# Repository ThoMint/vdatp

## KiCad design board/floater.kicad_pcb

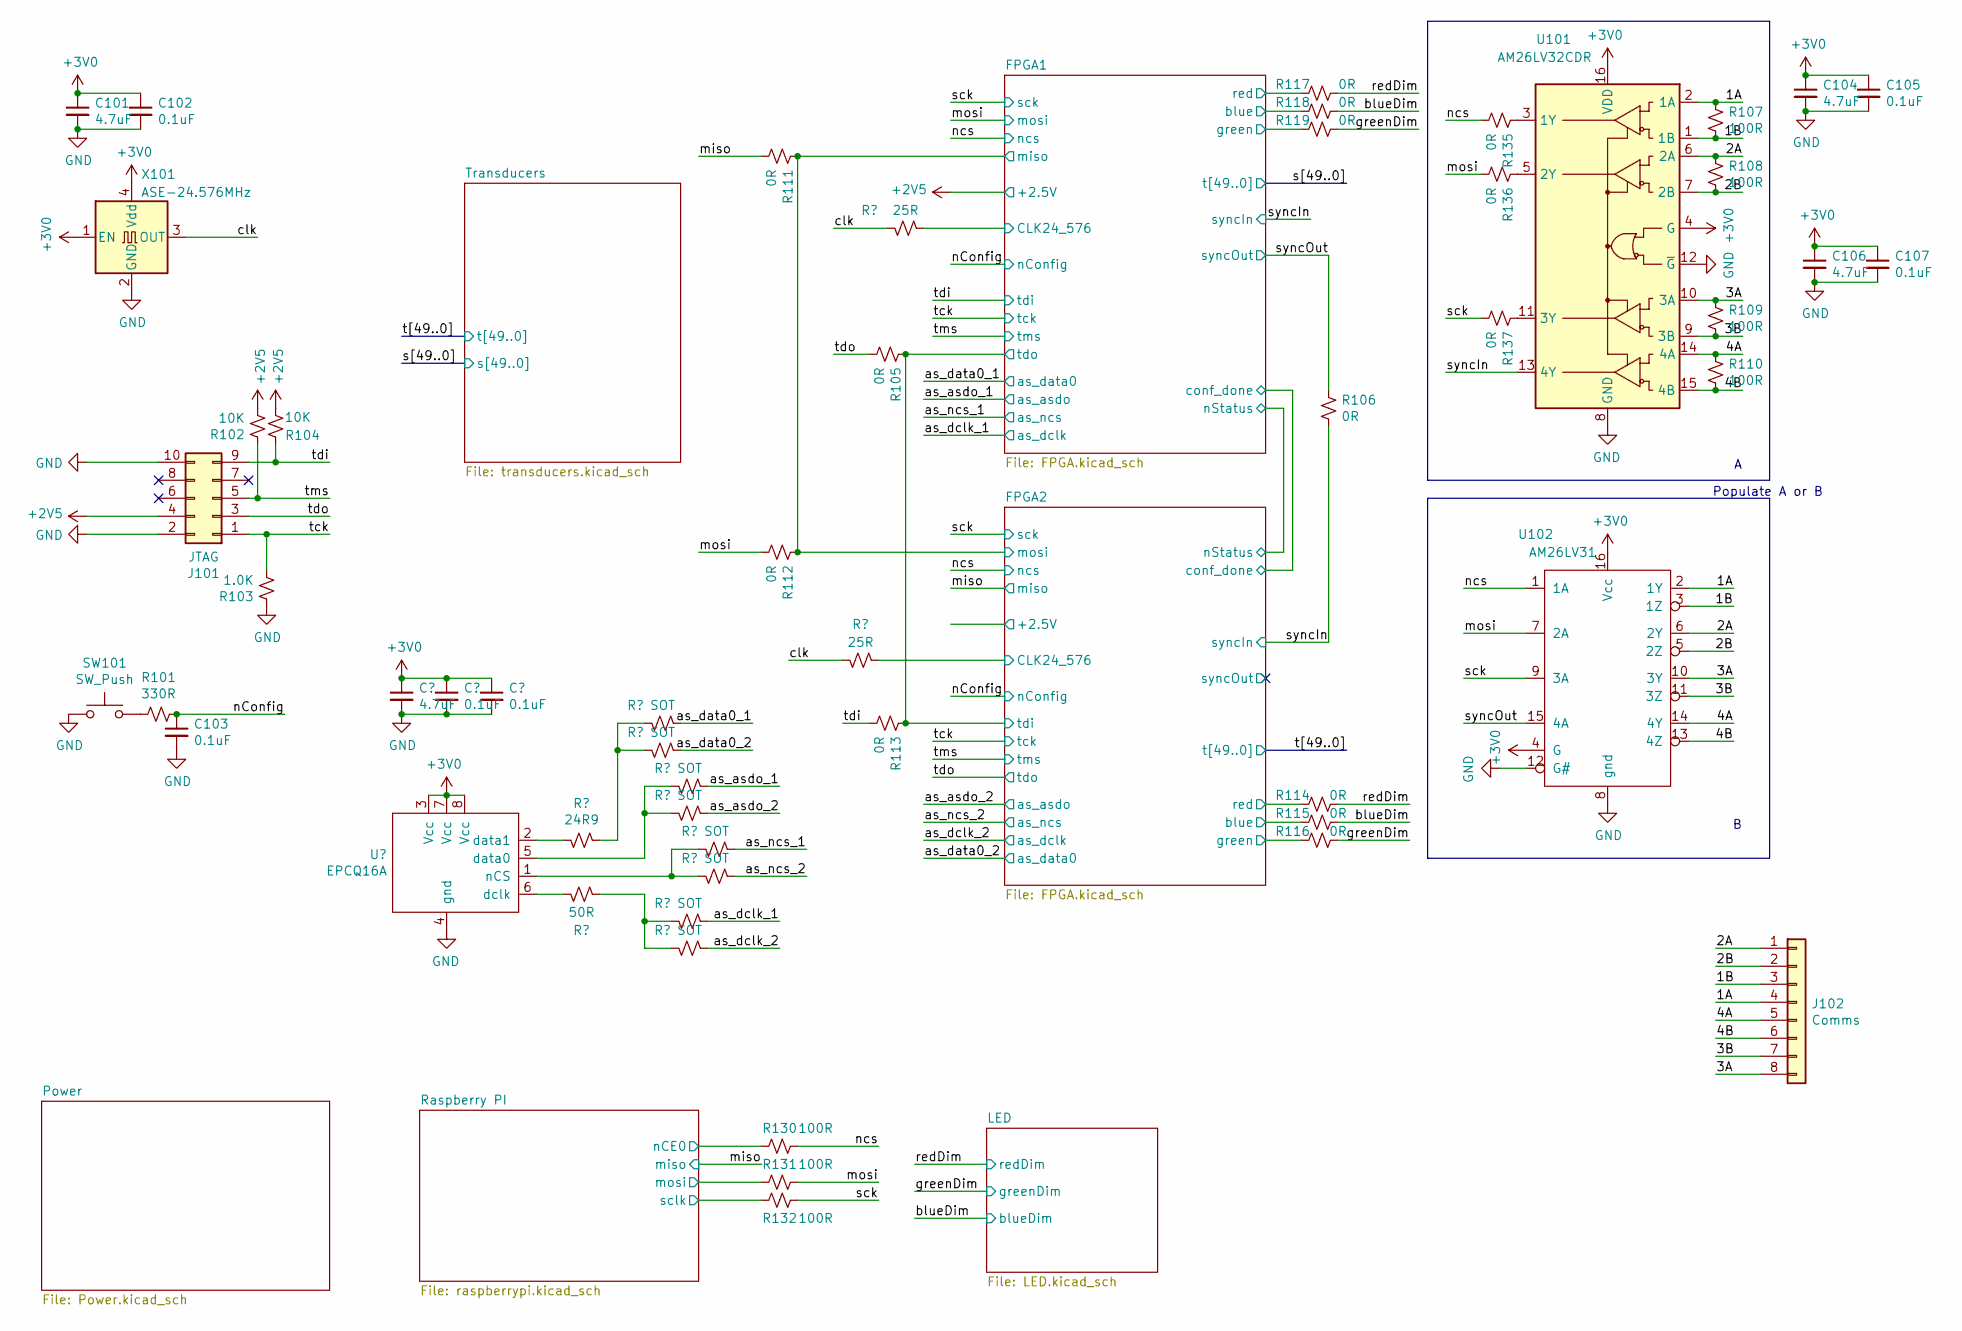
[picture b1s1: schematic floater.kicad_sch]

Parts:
C101, C104, C106, C108: 4.7uF; C_0603_1608Metric
C102, C103, C105, C107, C109, C110: 0.1uF; C_0402_1005Metric
J101: JTAG; PinHeader_2x05_P2.54mm_Vertical_Shrouded
J102: Comms; Hirose_DF13-08P-1.25DS_1x08_P1.25mm_Horizontal
R101: 330R; R_0402_1005Metric
R102, R104: 10K; R_0402_1005Metric
R103: 1.0K; R_0402_1005Metric
R105, R111, R112, R113, R114, R115, R116, R117, R118, R119, R135, R136, R137: 0R; R_0402_1005Metric
R106: 0R; SolderJumper-2_P1.3mm_Open_TrianglePad1.0x1.5mm
R107, R108, R109, R110, R130, R131, R132: 100R; R_0402_1005Metric
R120: 24R9; R_0402_1005Metric
R121: 50R; R_0402_1005Metric
R122, R123, R124, R125, R126, R127, R128, R129: SOT; R_0402_1005Metric
R133, R134: 25R; R_0402_1005Metric
SW101: SW_Push; SW_SPST_KMR2
U101: AM26LV32CDR; SOIC-16_3.9x9.9mm_P1.27mm
U102: AM26LV31; SOIC-16_3.9x9.9mm_P1.27mm
U103: EPCQ16A; SOIC-8_3.9x4.9mm_P1.27mm
X101: ASE-24.576MHz; ASFL1

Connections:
+3V0: C101.1, C102.1, C104.1, C105.1, C106.1, C107.1, C108.1, C109.1, C110.1, U101.4 (G), U101.16 (VDD), U102.4 (G), U102.16 (Vcc), U103.3 (Vcc), U103.7 (Vcc), U103.8 (Vcc), X101.1 (EN), X101.4 (Vdd); also elsewhere on the board
/1A: J102.4, R107.1, U101.2 (1A), U102.2 (1Y)
/1B: J102.3, R107.2, U101.1 (1B), U102.3 (1Z)
/2A: J102.1, R108.1, U101.6 (2A), U102.6 (2Y)
/2B: J102.2, R108.2, U101.7 (2B), U102.5 (2Z)
/3A: J102.8, R109.1, U101.10 (3A), U102.10 (3Y)
/3B: J102.7, R109.2, U101.9 (3B), U102.11 (3Z)
/4A: J102.5, R110.1, U101.14 (4A), U102.14 (4Y)
/4B: J102.6, R110.2, U101.15 (4B), U102.13 (4Z)
/FPGA1/CLK24_576: R134.2; also elsewhere on the board
/FPGA1/blue: R118.2; also elsewhere on the board
/FPGA1/green: R119.2; also elsewhere on the board
/FPGA1/miso: R111.1, R112.1; also elsewhere on the board
/FPGA1/red: R117.2; also elsewhere on the board
/FPGA2/CLK24_576: R133.2; also elsewhere on the board
/FPGA2/blue: R115.2; also elsewhere on the board
/FPGA2/green: R116.2; also elsewhere on the board
/FPGA2/red: R114.2; also elsewhere on the board
/FPGA2/tdi: R105.1, R113.1; also elsewhere on the board
/Raspberry PI/mosi: R131.2; also elsewhere on the board
/Raspberry PI/nCE0: R130.2; also elsewhere on the board
/Raspberry PI/sclk: R132.2; also elsewhere on the board
/as_asdo_1: R124.2; also elsewhere on the board
/as_asdo_2: R125.2; also elsewhere on the board
/as_data0_1: R122.2; also elsewhere on the board
/as_data0_2: R123.2; also elsewhere on the board
/as_dclk_1: R126.2; also elsewhere on the board
/as_dclk_2: R127.2; also elsewhere on the board
/as_ncs_1: R128.2; also elsewhere on the board
/as_ncs_2: R129.2; also elsewhere on the board
/blueDim: R115.1, R118.1; also elsewhere on the board
/clk: R133.1, R134.1, X101.3 (OUT)
/greenDim: R116.1, R119.1; also elsewhere on the board
/miso: R111.2; also elsewhere on the board
/mosi: R112.2, R131.1, R136.2, U102.7 (2A); also elsewhere on the board
/nConfig: C103.1, R101.2; also elsewhere on the board
/ncs: R130.1, R135.2, U102.1 (1A); also elsewhere on the board
/redDim: R114.1, R117.1; also elsewhere on the board
/sck: R132.1, R137.2, U102.9 (3A); also elsewhere on the board
/syncIn: R106.2, U101.13 (4Y); also elsewhere on the board
/syncOut: R106.1, U102.15 (4A); also elsewhere on the board
/tck: J101.1, R103.2; also elsewhere on the board
/tdi: J101.9, R104.1, R113.2; also elsewhere on the board
/tdo: J101.3, R105.2; also elsewhere on the board
/tms: J101.5, R102.1; also elsewhere on the board
GND: C101.2, C102.2, C103.2, C104.2, C105.2, C106.2, C107.2, C108.2, C109.2, C110.2, J101.2, J101.10, R103.1, SW101.1, U101.8 (GND), U101.12 (~G), U102.8 (gnd), U102.12 (G#), U103.4 (gnd), X101.2 (GND); also elsewhere on the board
unnamed: R101.1, SW101.2
unnamed: R120.1, U103.2 (data1)
unnamed: R120.2, R122.1, R123.1
unnamed: R121.1, U103.6 (dclk)
unnamed: R121.2, R126.1, R127.1
unnamed: R124.1, R125.1, U103.5 (data0)
unnamed: R128.1, R129.1, U103.1 (nCS)
unnamed: R135.1, U101.3 (1Y)
unnamed: R136.1, U101.5 (2Y)
unnamed: R137.1, U101.11 (3Y)

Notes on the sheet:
Populate A or B

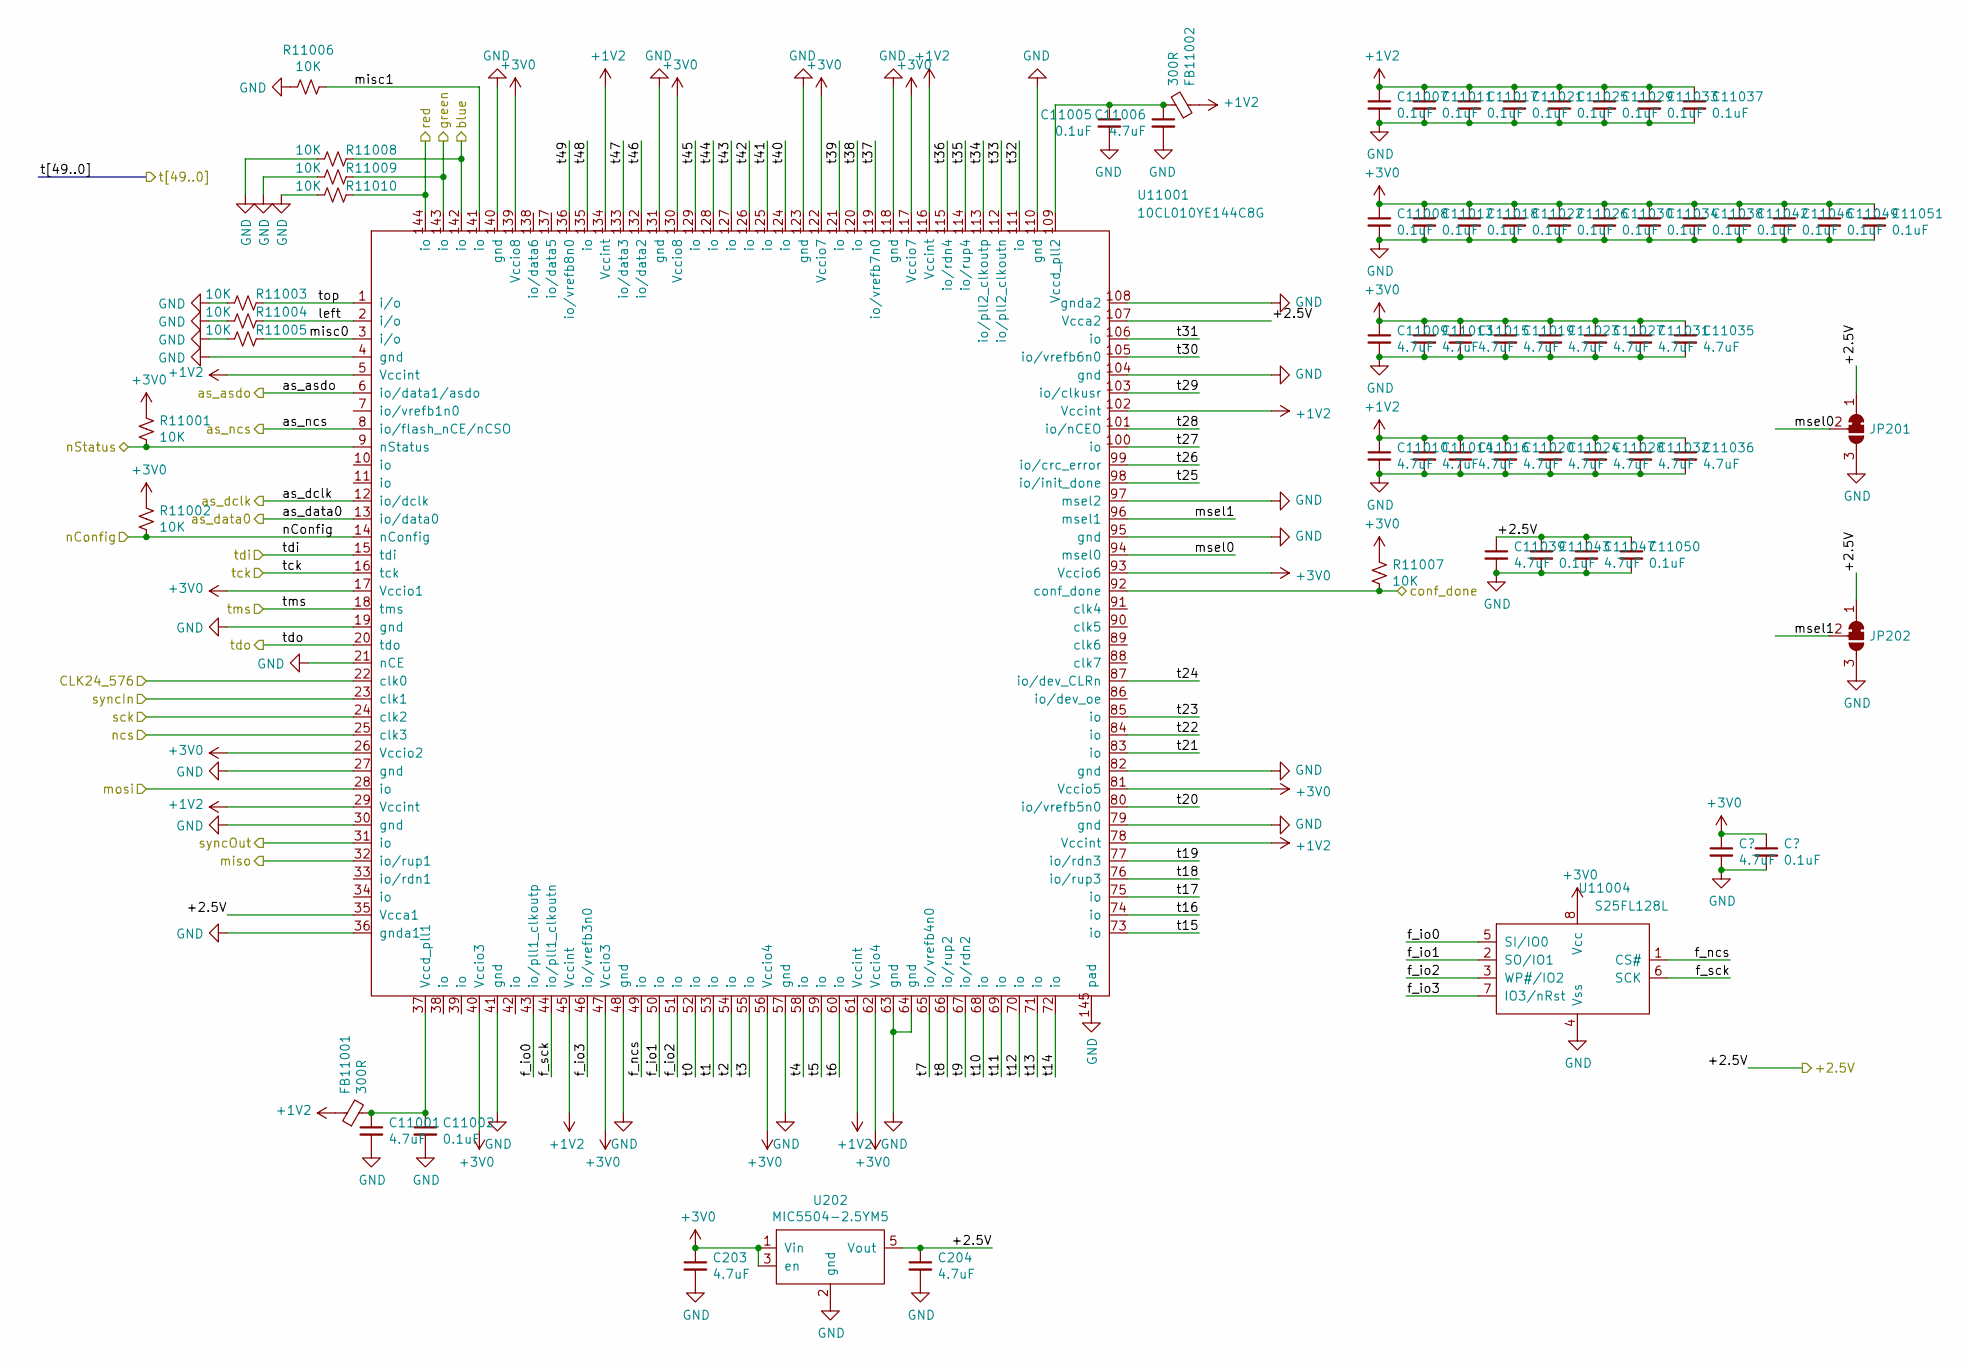
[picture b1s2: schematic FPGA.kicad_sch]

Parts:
C203, C204, C241, C11001, C11006, C11009, C11010, C11013, C11014, C11015, C11016, C11019, C11020, C11023, C11024, C11027, C11028, C11031, C11032, C11035, C11036, C11039, C11047: 4.7uF; C_0603_1608Metric
C245, C11002, C11005, C11007, C11008, C11011, C11012, C11017, C11018, C11021, C11022, C11025, C11026, C11029, C11030, C11033, C11034, C11037, C11038, C11042, C11043, C11046, C11049, C11050, C11051: 0.1uF; C_0402_1005Metric
FB11001, FB11002: 300R; R_0402_1005Metric
JP201, JP202: SolderJumper_3_Bridged12; SolderJumper-3_bridged12
R11001, R11002, R11003, R11004, R11005, R11006, R11007, R11008, R11009, R11010: 10K; R_0402_1005Metric
U202: MIC5504-2.5YM5; SOT-23-5
U11001: 10CL010YE144C8G; EQFP-144-1EP_20x20mm_P0.5mm_EP6.7x6.7mm
U11004: S25FL128L; SOIC-8_5.275x5.275mm_P1.27mm

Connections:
+1V2: C11007.1, C11010.1, C11011.1, C11014.1, C11016.1, C11017.1, C11020.1, C11021.1, C11024.1, C11025.1, C11028.1, C11029.1, C11032.1, C11033.1, C11036.1, C11037.1, FB11001.1, FB11002.1, U11001.5 (Vccint), U11001.29 (Vccint), U11001.45 (Vccint), U11001.61 (Vccint), U11001.78 (Vccint), U11001.102 (Vccint), U11001.116 (Vccint), U11001.134 (Vccint); also elsewhere on the board
+3V0: C203.1, C241.1, C245.1, C11008.1, C11009.1, C11012.1, C11013.1, C11015.1, C11018.1, C11019.1, C11022.1, C11023.1, C11026.1, C11027.1, C11030.1, C11031.1, C11034.1, C11035.1, C11038.1, C11042.1, C11046.1, C11049.1, C11051.1, R11001.2, R11002.2, R11007.2, U202.1 (Vin), U202.3 (en), U11001.17 (Vccio1), U11001.26 (Vccio2), U11001.40 (Vccio3), U11001.47 (Vccio3), U11001.56 (Vccio4), U11001.62 (Vccio4), U11001.81 (Vccio5), U11001.93 (Vccio6), U11001.117 (Vccio7), U11001.122 (Vccio7), U11001.130 (Vccio8), U11001.139 (Vccio8), U11004.8 (Vcc); also elsewhere on the board
/FPGA1/conf_done: R11007.1, U11001.92 (conf_done); also elsewhere on the board
/FPGA1/miso: U11001.28 (io); also elsewhere on the board
/FPGA1/nStatus: R11001.1, U11001.9 (nStatus); also elsewhere on the board
/FPGA2/CLK24_576: U11001.22 (clk0); also elsewhere on the board
/FPGA2/blue: R11008.2, U11001.142 (io); also elsewhere on the board
/FPGA2/f_io0: U11001.43 (io/pll1_clkoutp), U11004.5 (SI/IO0)
/FPGA2/f_io1: U11001.50 (io), U11004.2 (SO/IO1)
/FPGA2/f_io2: U11001.51 (io), U11004.3 (WP#/IO2)
/FPGA2/f_io3: U11001.46 (io/vrefb3n0), U11004.7 (IO3/nRst)
/FPGA2/f_ncs: U11001.49 (io), U11004.1 (CS#)
/FPGA2/f_sck: U11001.44 (io/pll1_clkoutn), U11004.6 (SCK)
/FPGA2/green: R11009.2, U11001.143 (io); also elsewhere on the board
/FPGA2/left: R11004.2, U11001.2 (i/o)
/FPGA2/misc0: R11005.2, U11001.3 (i/o)
/FPGA2/misc1: R11006.2, U11001.141 (io)
/FPGA2/red: R11010.2, U11001.144 (io); also elsewhere on the board
/FPGA2/syncOut: U11001.31 (io)
/FPGA2/t0: U11001.52 (io); also elsewhere on the board
/FPGA2/t1: U11001.53 (io); also elsewhere on the board
/FPGA2/t2: U11001.54 (io); also elsewhere on the board
/FPGA2/t3: U11001.55 (io); also elsewhere on the board
/FPGA2/t4: U11001.58 (io); also elsewhere on the board
/FPGA2/t5: U11001.59 (io); also elsewhere on the board
/FPGA2/t6: U11001.60 (io); also elsewhere on the board
/FPGA2/t7: U11001.65 (io/vrefb4n0); also elsewhere on the board
/FPGA2/t8: U11001.66 (io/rup2); also elsewhere on the board
/FPGA2/t9: U11001.67 (io/rdn2); also elsewhere on the board
/FPGA2/t10: U11001.68 (io); also elsewhere on the board
/FPGA2/t11: U11001.69 (io); also elsewhere on the board
/FPGA2/t12: U11001.70 (io); also elsewhere on the board
/FPGA2/t13: U11001.71 (io); also elsewhere on the board
/FPGA2/t14: U11001.72 (io); also elsewhere on the board
/FPGA2/t15: U11001.73 (io); also elsewhere on the board
/FPGA2/t16: U11001.74 (io); also elsewhere on the board
/FPGA2/t17: U11001.75 (io); also elsewhere on the board
/FPGA2/t18: U11001.76 (io/rup3); also elsewhere on the board
/FPGA2/t19: U11001.77 (io/rdn3); also elsewhere on the board
/FPGA2/t20: U11001.80 (io/vrefb5n0); also elsewhere on the board
/FPGA2/t21: U11001.83 (io); also elsewhere on the board
/FPGA2/t22: U11001.84 (io); also elsewhere on the board
/FPGA2/t23: U11001.85 (io); also elsewhere on the board
/FPGA2/t24: U11001.87 (io/dev_CLRn); also elsewhere on the board
/FPGA2/t25: U11001.98 (io/init_done); also elsewhere on the board
/FPGA2/t26: U11001.99 (io/crc_error); also elsewhere on the board
/FPGA2/t27: U11001.100 (io); also elsewhere on the board
/FPGA2/t28: U11001.101 (io/nCEO); also elsewhere on the board
/FPGA2/t29: U11001.103 (io/clkusr); also elsewhere on the board
/FPGA2/t30: U11001.105 (io/vrefb6n0); also elsewhere on the board
/FPGA2/t31: U11001.106 (io); also elsewhere on the board
/FPGA2/t32: U11001.111 (io); also elsewhere on the board
/FPGA2/t33: U11001.112 (io/pll2_clkoutn); also elsewhere on the board
/FPGA2/t34: U11001.113 (io/pll2_clkoutp); also elsewhere on the board
/FPGA2/t35: U11001.114 (io/rup4); also elsewhere on the board
/FPGA2/t36: U11001.115 (io/rdn4); also elsewhere on the board
/FPGA2/t37: U11001.119 (io/vrefb7n0); also elsewhere on the board
/FPGA2/t38: U11001.120 (io); also elsewhere on the board
/FPGA2/t39: U11001.121 (io); also elsewhere on the board
/FPGA2/t40: U11001.124 (io); also elsewhere on the board
/FPGA2/t41: U11001.125 (io); also elsewhere on the board
/FPGA2/t42: U11001.126 (io); also elsewhere on the board
/FPGA2/t43: U11001.127 (io); also elsewhere on the board
/FPGA2/t44: U11001.128 (io); also elsewhere on the board
/FPGA2/t45: U11001.129 (io); also elsewhere on the board
/FPGA2/t46: U11001.132 (io/data2); also elsewhere on the board
/FPGA2/t47: U11001.133 (io/data3); also elsewhere on the board
/FPGA2/t48: U11001.135 (io); also elsewhere on the board
/FPGA2/t49: U11001.136 (io/vrefb8n0); also elsewhere on the board
/FPGA2/tdi: U11001.15 (tdi); also elsewhere on the board
/FPGA2/top: R11003.2, U11001.1 (i/o)
/as_asdo_2: U11001.6 (io/data1/asdo); also elsewhere on the board
/as_data0_2: U11001.13 (io/data0); also elsewhere on the board
/as_dclk_2: U11001.12 (io/dclk); also elsewhere on the board
/as_ncs_2: U11001.8 (io/flash_nCE/nCSO); also elsewhere on the board
/miso: U11001.32 (io/rup1); also elsewhere on the board
/nConfig: R11002.1, U11001.14 (nConfig); also elsewhere on the board
/ncs: U11001.25 (clk3); also elsewhere on the board
/sck: U11001.24 (clk2); also elsewhere on the board
/syncIn: U11001.23 (clk1); also elsewhere on the board
/tck: U11001.16 (tck); also elsewhere on the board
/tdo: U11001.20 (tdo); also elsewhere on the board
/tms: U11001.18 (tms); also elsewhere on the board
GND: C203.2, C204.2, C241.2, C245.2, C11001.2, C11002.2, C11005.2, C11006.2, C11007.2, C11008.2, C11009.2, C11010.2, C11011.2, C11012.2, C11013.2, C11014.2, C11015.2, C11016.2, C11017.2, C11018.2, C11019.2, C11020.2, C11021.2, C11022.2, C11023.2, C11024.2, C11025.2, C11026.2, C11027.2, C11028.2, C11029.2, C11030.2, C11031.2, C11032.2, C11033.2, C11034.2, C11035.2, C11036.2, C11037.2, C11038.2, C11039.2, C11042.2, C11043.2, C11046.2, C11047.2, C11049.2, C11050.2, C11051.2, JP201.3 (B), JP202.3 (B), R11003.1, R11004.1, R11005.1, R11006.1, R11008.1, R11009.1, R11010.1, U202.2 (gnd), U11001.4 (gnd), U11001.19 (gnd), U11001.21 (nCE), U11001.27 (gnd), U11001.30 (gnd), U11001.36 (gnda1), U11001.41 (gnd), U11001.48 (gnd), U11001.57 (gnd), U11001.63 (gnd), U11001.64 (gnd), U11001.79 (gnd), U11001.82 (gnd), U11001.95 (gnd), U11001.97 (msel2), U11001.104 (gnd), U11001.108 (gnda2), U11001.110 (gnd), U11001.118 (gnd), U11001.123 (gnd), U11001.131 (gnd), U11001.140 (gnd), U11001.145 (pad), U11004.4 (Vss); also elsewhere on the board
unnamed: C11001.1, C11002.1, FB11001.2, U11001.37 (Vccd_pll1)
unnamed: C11005.1, C11006.1, FB11002.2, U11001.109 (Vccd_pll2)

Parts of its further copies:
C201, C206, C209, C210, C213, C214, C215, C216, C219, C220, C223, C224, C227, C228, C231, C232, C235, C236, C239, C247, C11003, C11004, C11041: 4.7uF; C_0603_1608Metric
C202, C205, C207, C208, C211, C212, C217, C218, C221, C222, C225, C226, C229, C230, C233, C234, C237, C238, C242, C243, C246, C249, C250, C251, C11045: 0.1uF; C_0402_1005Metric
FB201, FB202: 300R; R_0402_1005Metric
JP11001, JP11002: SolderJumper_3_Bridged12; SolderJumper-3_bridged12
R201, R202, R203, R204, R205, R206, R207, R208, R209, R210: 10K; R_0402_1005Metric
U201: 10CL010YE144C8G; EQFP-144-1EP_20x20mm_P0.5mm_EP6.7x6.7mm
U204: S25FL128L; SOIC-8_5.275x5.275mm_P1.27mm
U11002: MIC5504-2.5YM5; SOT-23-5

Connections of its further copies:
+1V2: C207.1, C210.1, C211.1, C214.1, C216.1, C217.1, C220.1, C221.1, C224.1, C225.1, C228.1, C229.1, C232.1, C233.1, C236.1, C237.1, FB201.1, FB202.1, U201.5 (Vccint), U201.29 (Vccint), U201.45 (Vccint), U201.61 (Vccint), U201.78 (Vccint), U201.102 (Vccint), U201.116 (Vccint), U201.134 (Vccint); also elsewhere on the board
+3V0: C208.1, C209.1, C212.1, C213.1, C215.1, C218.1, C219.1, C222.1, C223.1, C226.1, C227.1, C230.1, C231.1, C234.1, C235.1, C238.1, C242.1, C246.1, C249.1, C251.1, C11003.1, C11041.1, C11045.1, R201.2, R202.2, R207.2, U201.17 (Vccio1), U201.26 (Vccio2), U201.40 (Vccio3), U201.47 (Vccio3), U201.56 (Vccio4), U201.62 (Vccio4), U201.81 (Vccio5), U201.93 (Vccio6), U201.117 (Vccio7), U201.122 (Vccio7), U201.130 (Vccio8), U201.139 (Vccio8), U204.8 (Vcc), U11002.1 (Vin), U11002.3 (en); also elsewhere on the board
/FPGA1/CLK24_576: U201.22 (clk0); also elsewhere on the board
/FPGA1/blue: R208.2, U201.142 (io); also elsewhere on the board
/FPGA1/conf_done: R207.1, U201.92 (conf_done); also elsewhere on the board
/FPGA1/f_io0: U201.43 (io/pll1_clkoutp), U204.5 (SI/IO0)
/FPGA1/f_io1: U201.50 (io), U204.2 (SO/IO1)
/FPGA1/f_io2: U201.51 (io), U204.3 (WP#/IO2)
/FPGA1/f_io3: U201.46 (io/vrefb3n0), U204.7 (IO3/nRst)
/FPGA1/f_ncs: U201.49 (io), U204.1 (CS#)
/FPGA1/f_sck: U201.44 (io/pll1_clkoutn), U204.6 (SCK)
/FPGA1/green: R209.2, U201.143 (io); also elsewhere on the board
/FPGA1/left: R204.2, U201.2 (i/o)
/FPGA1/misc0: R205.2, U201.3 (i/o)
/FPGA1/misc1: R206.2, U201.141 (io)
/FPGA1/miso: U201.32 (io/rup1); also elsewhere on the board
/FPGA1/nStatus: R201.1, U201.9 (nStatus); also elsewhere on the board
/FPGA1/red: R210.2, U201.144 (io); also elsewhere on the board
/FPGA1/top: R203.2, U201.1 (i/o)
/FPGA2/tdi: U201.20 (tdo); also elsewhere on the board
/Transducers/s0: U201.52 (io); also elsewhere on the board
/Transducers/s1: U201.53 (io); also elsewhere on the board
/Transducers/s2: U201.54 (io); also elsewhere on the board
/Transducers/s3: U201.55 (io); also elsewhere on the board
/Transducers/s4: U201.58 (io); also elsewhere on the board
/Transducers/s5: U201.59 (io); also elsewhere on the board
/Transducers/s6: U201.60 (io); also elsewhere on the board
/Transducers/s7: U201.65 (io/vrefb4n0); also elsewhere on the board
/Transducers/s8: U201.66 (io/rup2); also elsewhere on the board
/Transducers/s9: U201.67 (io/rdn2); also elsewhere on the board
/Transducers/s10: U201.68 (io); also elsewhere on the board
/Transducers/s11: U201.69 (io); also elsewhere on the board
/Transducers/s12: U201.70 (io); also elsewhere on the board
/Transducers/s13: U201.71 (io); also elsewhere on the board
/Transducers/s14: U201.72 (io); also elsewhere on the board
/Transducers/s15: U201.73 (io); also elsewhere on the board
/Transducers/s16: U201.74 (io); also elsewhere on the board
/Transducers/s17: U201.75 (io); also elsewhere on the board
/Transducers/s18: U201.76 (io/rup3); also elsewhere on the board
/Transducers/s19: U201.77 (io/rdn3); also elsewhere on the board
/Transducers/s20: U201.80 (io/vrefb5n0); also elsewhere on the board
/Transducers/s21: U201.83 (io); also elsewhere on the board
/Transducers/s22: U201.84 (io); also elsewhere on the board
/Transducers/s23: U201.85 (io); also elsewhere on the board
/Transducers/s24: U201.87 (io/dev_CLRn); also elsewhere on the board
/Transducers/s25: U201.98 (io/init_done); also elsewhere on the board
/Transducers/s26: U201.99 (io/crc_error); also elsewhere on the board
/Transducers/s27: U201.100 (io); also elsewhere on the board
/Transducers/s28: U201.101 (io/nCEO); also elsewhere on the board
/Transducers/s29: U201.103 (io/clkusr); also elsewhere on the board
/Transducers/s30: U201.105 (io/vrefb6n0); also elsewhere on the board
/Transducers/s31: U201.106 (io); also elsewhere on the board
/Transducers/s32: U201.111 (io); also elsewhere on the board
/Transducers/s33: U201.112 (io/pll2_clkoutn); also elsewhere on the board
/Transducers/s34: U201.113 (io/pll2_clkoutp); also elsewhere on the board
/Transducers/s35: U201.114 (io/rup4); also elsewhere on the board
/Transducers/s36: U201.115 (io/rdn4); also elsewhere on the board
/Transducers/s37: U201.119 (io/vrefb7n0); also elsewhere on the board
/Transducers/s38: U201.120 (io); also elsewhere on the board
/Transducers/s39: U201.121 (io); also elsewhere on the board
/Transducers/s40: U201.124 (io); also elsewhere on the board
/Transducers/s41: U201.125 (io); also elsewhere on the board
/Transducers/s42: U201.126 (io); also elsewhere on the board
/Transducers/s43: U201.127 (io); also elsewhere on the board
/Transducers/s44: U201.128 (io); also elsewhere on the board
/Transducers/s45: U201.129 (io); also elsewhere on the board
/Transducers/s46: U201.132 (io/data2); also elsewhere on the board
/Transducers/s47: U201.133 (io/data3); also elsewhere on the board
/Transducers/s48: U201.135 (io); also elsewhere on the board
/Transducers/s49: U201.136 (io/vrefb8n0); also elsewhere on the board
/as_asdo_1: U201.6 (io/data1/asdo); also elsewhere on the board
/as_data0_1: U201.13 (io/data0); also elsewhere on the board
/as_dclk_1: U201.12 (io/dclk); also elsewhere on the board
/as_ncs_1: U201.8 (io/flash_nCE/nCSO); also elsewhere on the board
/mosi: U201.28 (io); also elsewhere on the board
/nConfig: R202.1, U201.14 (nConfig); also elsewhere on the board
/ncs: U201.25 (clk3); also elsewhere on the board
/sck: U201.24 (clk2); also elsewhere on the board
/syncIn: U201.23 (clk1); also elsewhere on the board
/syncOut: U201.31 (io); also elsewhere on the board
/tck: U201.16 (tck); also elsewhere on the board
/tdi: U201.15 (tdi); also elsewhere on the board
/tms: U201.18 (tms); also elsewhere on the board
GND: C201.2, C202.2, C205.2, C206.2, C207.2, C208.2, C209.2, C210.2, C211.2, C212.2, C213.2, C214.2, C215.2, C216.2, C217.2, C218.2, C219.2, C220.2, C221.2, C222.2, C223.2, C224.2, C225.2, C226.2, C227.2, C228.2, C229.2, C230.2, C231.2, C232.2, C233.2, C234.2, C235.2, C236.2, C237.2, C238.2, C239.2, C242.2, C243.2, C246.2, C247.2, C249.2, C250.2, C251.2, C11003.2, C11004.2, C11041.2, C11045.2, JP11001.3 (B), JP11002.3 (B), R203.1, R204.1, R205.1, R206.1, R208.1, R209.1, R210.1, U201.4 (gnd), U201.19 (gnd), U201.21 (nCE), U201.27 (gnd), U201.30 (gnd), U201.36 (gnda1), U201.41 (gnd), U201.48 (gnd), U201.57 (gnd), U201.63 (gnd), U201.64 (gnd), U201.79 (gnd), U201.82 (gnd), U201.95 (gnd), U201.97 (msel2), U201.104 (gnd), U201.108 (gnda2), U201.110 (gnd), U201.118 (gnd), U201.123 (gnd), U201.131 (gnd), U201.140 (gnd), U201.145 (pad), U204.4 (Vss), U11002.2 (gnd); also elsewhere on the board
unnamed: C201.1, C202.1, FB201.2, U201.37 (Vccd_pll1)
unnamed: C205.1, C206.1, FB202.2, U201.109 (Vccd_pll2)

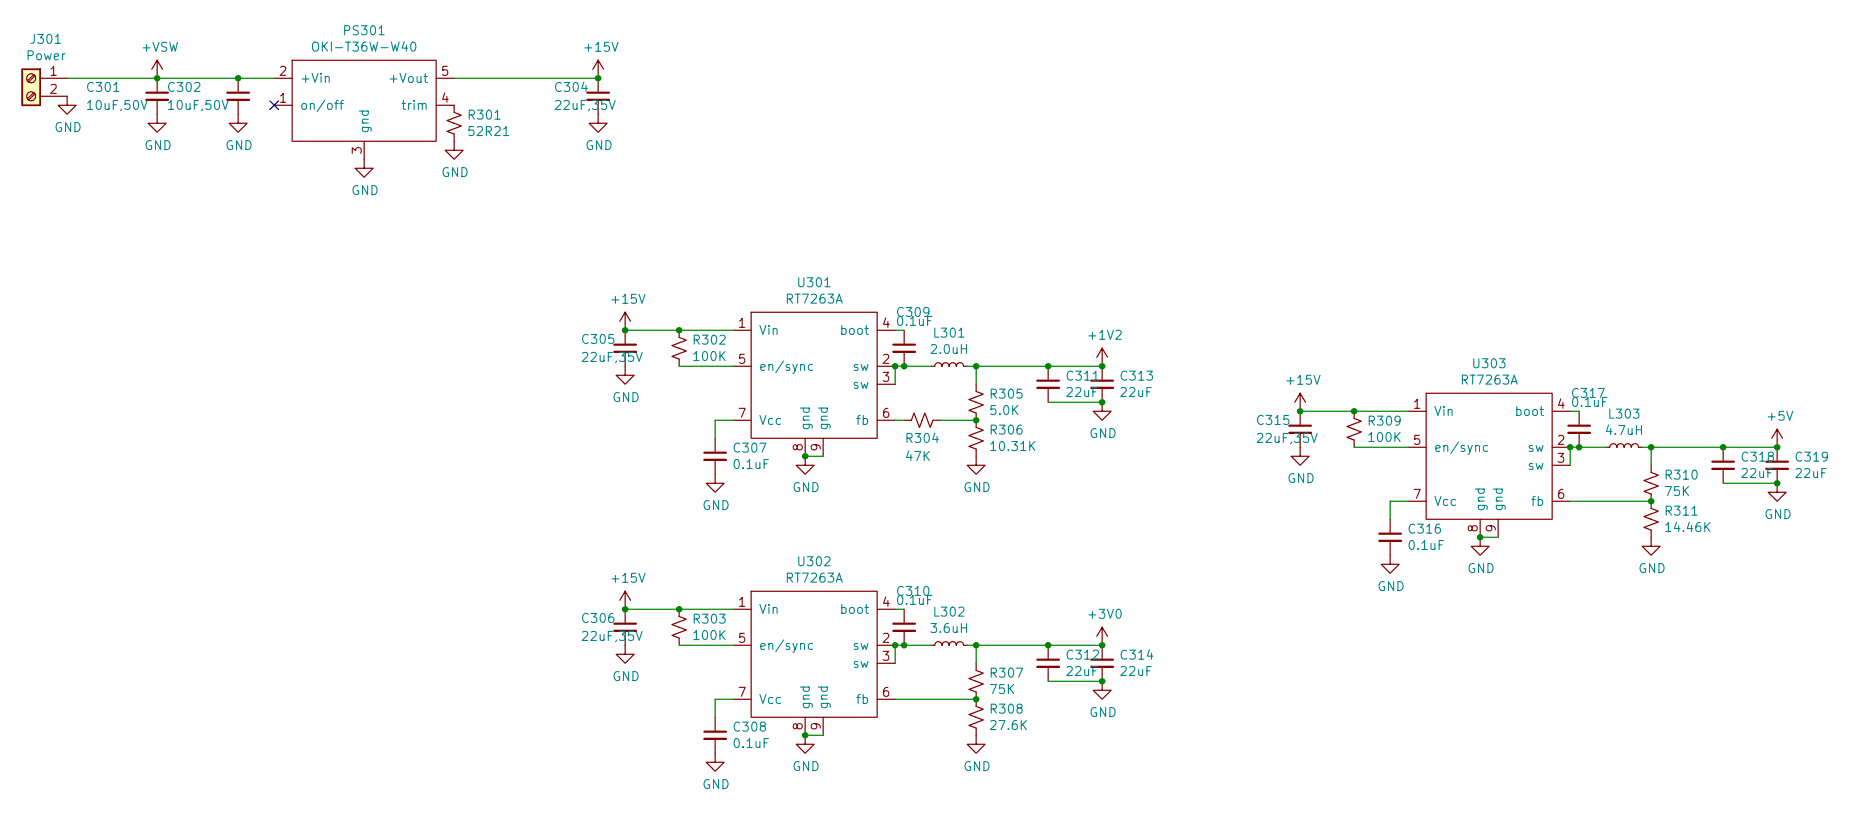
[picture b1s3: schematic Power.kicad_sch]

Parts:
C301, C302: 10uF,50V; R_1210_3225Metric
C304, C305, C306, C315: 22uF,35V; C_1210_3225Metric
C307, C308, C309, C310, C316, C317: 0.1uF; C_0402_1005Metric
C311, C312, C313, C314, C318, C319: 22uF; C_1210_3225Metric
J301: Power; Molex_70555_RA_1x02_P2.54
L301: 2.0uH; NR8040
L302: 3.6uH; NR8040
L303: 4.7uH; NR8040
PS301: OKI-T36W-W40; OKI-T-36W-W40
R301: 52R21; R_0603_1608Metric
R302, R303, R309: 100K; R_0402_1005Metric
R304: 47K; R_0402_1005Metric
R305: 5.0K; R_0402_1005Metric
R306: 10.31K; R_0402_1005Metric
R307, R310: 75K; R_0402_1005Metric
R308: 27.6K; R_0402_1005Metric
R311: 14.46K; R_0402_1005Metric
U301, U302, U303: RT7263A; SOP-EP-8_3.9x4.9mm_P1.27mm

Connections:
+1V2: C311.1, C313.1, L301.2, R305.1; also elsewhere on the board
+3V0: C312.1, C314.1, L302.2, R307.1; also elsewhere on the board
+5V: C318.1, C319.1, L303.2, R310.1; also elsewhere on the board
+15V: C304.1, C305.1, C306.1, C315.1, PS301.5 (+Vout), R302.1, R303.1, R309.1, U301.1 (Vin), U302.1 (Vin), U303.1 (Vin); also elsewhere on the board
+VSW: C301.1, C302.1, J301.1, PS301.2 (+Vin); also elsewhere on the board
GND: C301.2, C302.2, C304.2, C305.2, C306.2, C307.2, C308.2, C311.2, C312.2, C313.2, C314.2, C315.2, C316.2, C318.2, C319.2, J301.2, PS301.3 (gnd), R301.2, R306.2, R308.2, R311.2, U301.8 (gnd), U301.9 (gnd), U302.8 (gnd), U302.9 (gnd), U303.8 (gnd), U303.9 (gnd); also elsewhere on the board
unnamed: C307.1, U301.7 (Vcc)
unnamed: C308.1, U302.7 (Vcc)
unnamed: C309.1, U301.4 (boot)
unnamed: C309.2, L301.1, U301.2 (sw), U301.3 (sw)
unnamed: C310.1, U302.4 (boot)
unnamed: C310.2, L302.1, U302.2 (sw), U302.3 (sw)
unnamed: C316.1, U303.7 (Vcc)
unnamed: C317.1, U303.4 (boot)
unnamed: C317.2, L303.1, U303.2 (sw), U303.3 (sw)
unnamed: PS301.4 (trim), R301.1
unnamed: R302.2, U301.5 (en/sync)
unnamed: R303.2, U302.5 (en/sync)
unnamed: R304.1, R305.2, R306.1
unnamed: R304.2, U301.6 (fb)
unnamed: R307.2, R308.1, U302.6 (fb)
unnamed: R309.2, U303.5 (en/sync)
unnamed: R310.2, R311.1, U303.6 (fb)

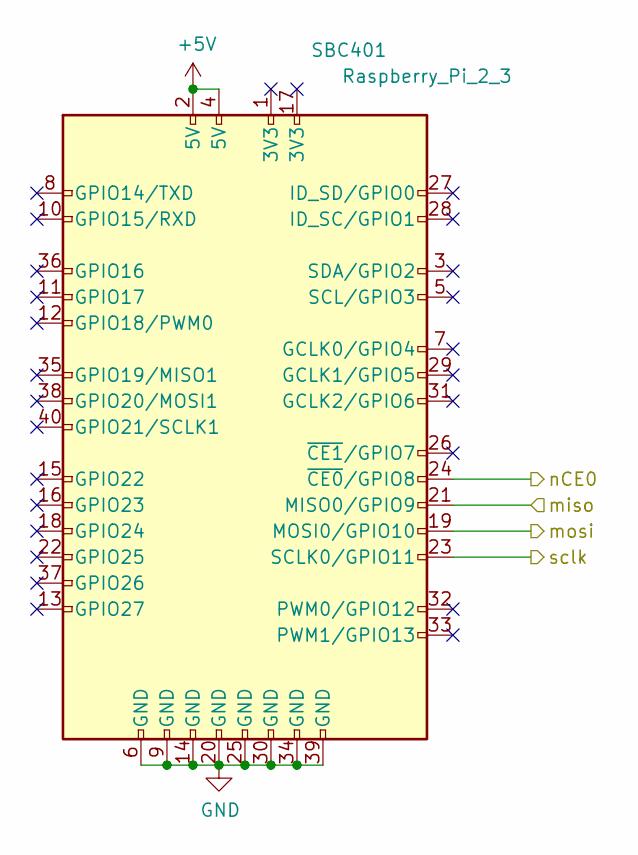
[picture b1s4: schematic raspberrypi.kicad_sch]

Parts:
SBC401: Raspberry_Pi_2_3; Raspberry_Pi_Zero_Socketed_THT_MountingHoles_SMT

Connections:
+5V: SBC401.2 (5V), SBC401.4 (5V); also elsewhere on the board
/Raspberry PI/mosi: SBC401.19 (MOSI0/GPIO10); also elsewhere on the board
/Raspberry PI/nCE0: SBC401.24 (~CE0/GPIO8); also elsewhere on the board
/Raspberry PI/sclk: SBC401.23 (SCLK0/GPIO11); also elsewhere on the board
/miso: SBC401.21 (MISO0/GPIO9); also elsewhere on the board
GND: SBC401.6 (GND), SBC401.9 (GND), SBC401.14 (GND), SBC401.20 (GND), SBC401.25 (GND), SBC401.30 (GND), SBC401.34 (GND), SBC401.39 (GND); also elsewhere on the board

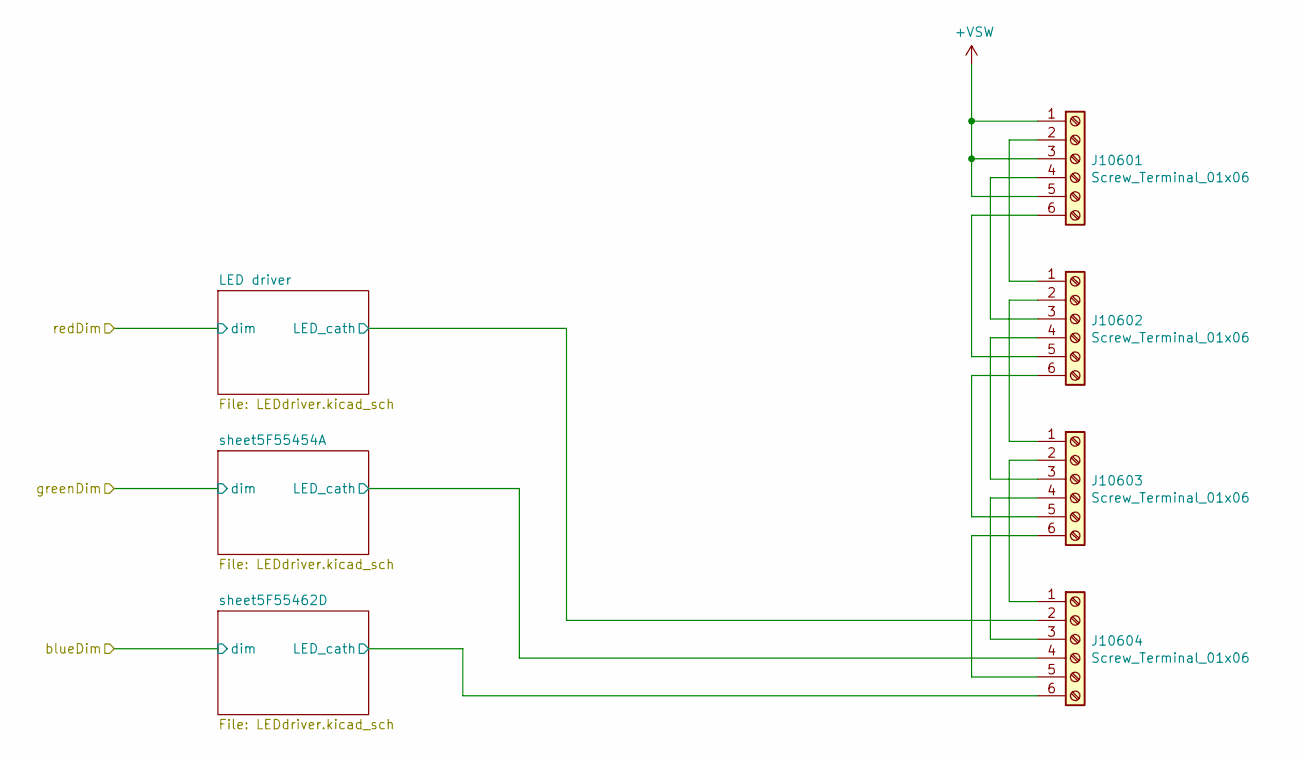
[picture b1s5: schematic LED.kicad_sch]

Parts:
J10601, J10602, J10603, J10604: Screw_Terminal_01x06; Hirose_DF13-06P-1.25DS_1x06_P1.25mm_Horizontal

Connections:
+VSW: J10601.1, J10601.3, J10601.5; also elsewhere on the board
/LED/LED driver/LED_cath: J10604.2; also elsewhere on the board
/LED/sheet5F55454A/LED_cath: J10604.4; also elsewhere on the board
/LED/sheet5F55462D/LED_cath: J10604.6; also elsewhere on the board
unnamed: J10601.2, J10602.1
unnamed: J10601.4, J10602.3
unnamed: J10601.6, J10602.5
unnamed: J10602.2, J10603.1
unnamed: J10602.4, J10603.3
unnamed: J10602.6, J10603.5
unnamed: J10603.2, J10604.1
unnamed: J10603.4, J10604.3
unnamed: J10603.6, J10604.5
